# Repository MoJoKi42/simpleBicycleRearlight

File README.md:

# simpleBicycleRearlight

It's was a quick project to get finally a working rear light for my bicycle. It uses 10x VLMK31R1S2 LEDs (red LEDs from VISHAY) driven with ~13mA constant current. The TS2509 Buck-Converter regulates the output voltage to get the constant current (see circuit diagram!).
PCB and Circuit was made with KiCad.

It works with a standard 6V bicyle dynamo. At my setup it's starts with flashing at slow cycle rotation and goes over to a constant brightness at higher rotations. The minimum needed voltage is about 3.5-4V (RMS).

The final assembly on my bicycle

Test with some green LEDs

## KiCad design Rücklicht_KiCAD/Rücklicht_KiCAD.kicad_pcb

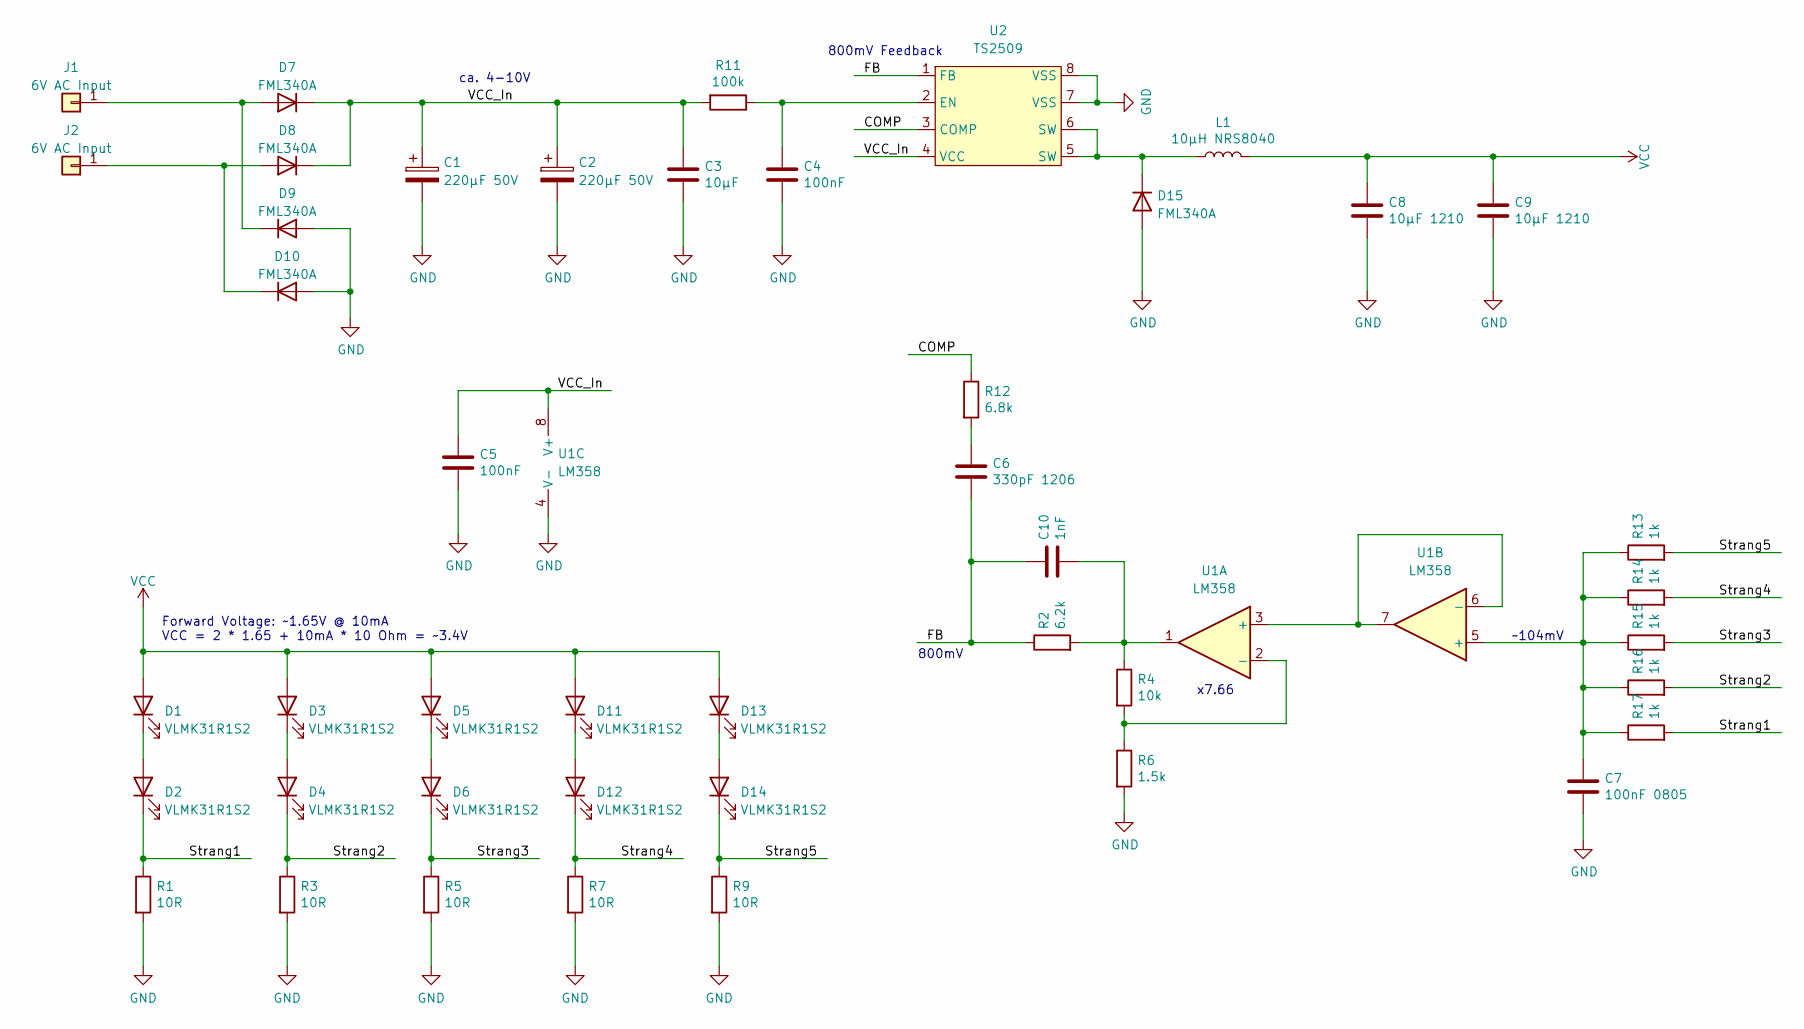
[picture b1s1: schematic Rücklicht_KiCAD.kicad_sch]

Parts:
C1, C2: 220µF 50V; C_Elec_10x10.2
C3: 10µF; C_1210_3225Metric_Pad1.33x2.70mm_HandSolder
C4, C5: 100nF; C_0805_2012Metric_Pad1.18x1.45mm_HandSolder
C6: 330pF 1206; C_1206_3216Metric_Pad1.33x1.80mm_HandSolder
C7: 100nF 0805; C_0805_2012Metric_Pad1.18x1.45mm_HandSolder
C8, C9: 10µF 1210; C_1210_3225Metric_Pad1.33x2.70mm_HandSolder
C10: 1nF; C_0805_2012Metric_Pad1.18x1.45mm_HandSolder
D1, D2, D3, D4, D5, D6, D11, D12, D13, D14: VLMK31R1S2; LED_PLCC-2
D7, D8, D9, D10, D15: FML340A; D_SMB_Handsoldering
J1, J2: 6V AC Input; TestPoint_Pad_3.0x3.0mm
L1: 10µH NRS8040; L_Taiyo-Yuden_NR-80xx_HandSoldering
R1, R3, R5, R7, R9: 10R; R_0805_2012Metric_Pad1.20x1.40mm_HandSolder
R2: 6.2k; R_0805_2012Metric_Pad1.20x1.40mm_HandSolder
R4: 10k; R_0805_2012Metric_Pad1.20x1.40mm_HandSolder
R6: 1.5k; R_0805_2012Metric_Pad1.20x1.40mm_HandSolder
R11: 100k; R_0805_2012Metric_Pad1.20x1.40mm_HandSolder
R12: 6.8k; R_0805_2012Metric_Pad1.20x1.40mm_HandSolder
R13, R14, R15, R16, R17: 1k; R_0805_2012Metric_Pad1.20x1.40mm_HandSolder
U1: LM358; SO-8_3.9x4.9mm_P1.27mm
U2: TS2509; SO-8_3.9x4.9mm_P1.27mm

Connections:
/COMP: R12.1, U2.3 (COMP)
/FB: C6.2, C10.1, R2.1, U2.1 (FB)
/Strang1: D2.1 (K), R1.1, R17.2
/Strang2: D4.1 (K), R3.1, R16.2
/Strang3: D6.1 (K), R5.1, R15.2
/Strang4: D12.1 (K), R7.1, R14.2
/Strang5: D14.1 (K), R9.1, R13.2
/VCC_In: C1.1, C2.1, C3.1, C5.1, D7.1 (K), D8.1 (K), R11.2, U1.8 (V+), U2.4 (VCC)
GND: C1.2, C2.2, C3.2, C4.2, C5.2, C7.2, C8.2, C9.2, D9.2 (A), D10.2 (A), D15.2 (A), R1.2, R3.2, R5.2, R6.2, R7.2, R9.2, U1.4 (V-), U2.7 (VSS), U2.8 (VSS)
unnamed: C4.1, R11.1, U2.2 (EN)
unnamed: C6.1, R12.2
unnamed: C7.1, R13.1, R14.1, R15.1, R16.1, R17.1, U1.5 (+)
unnamed: C10.2, R2.2, R4.1, U1.1
unnamed: D1.1 (K), D2.2 (A)
unnamed: D3.1 (K), D4.2 (A)
unnamed: D5.1 (K), D6.2 (A)
unnamed: D7.2 (A), D9.1 (K), J1.1
unnamed: D8.2 (A), D10.1 (K), J2.1
unnamed: D11.1 (K), D12.2 (A)
unnamed: D13.1 (K), D14.2 (A)
unnamed: D15.1 (K), L1.1, U2.5 (SW), U2.6 (SW)
unnamed: R4.2, R6.1, U1.2 (-)
unnamed: U1.3 (+), U1.6 (-), U1.7
VCC: C8.1, C9.1, D1.2 (A), D3.2 (A), D5.2 (A), D11.2 (A), D13.2 (A), L1.2

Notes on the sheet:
Forward Voltage: ~1.65V @ 10mA VCC = 2 * 1.65 + 10mA * 10 Ohm = ~3.4V
ca. 4-10V
800mV Feedback
800mV
x7.66
~104mV

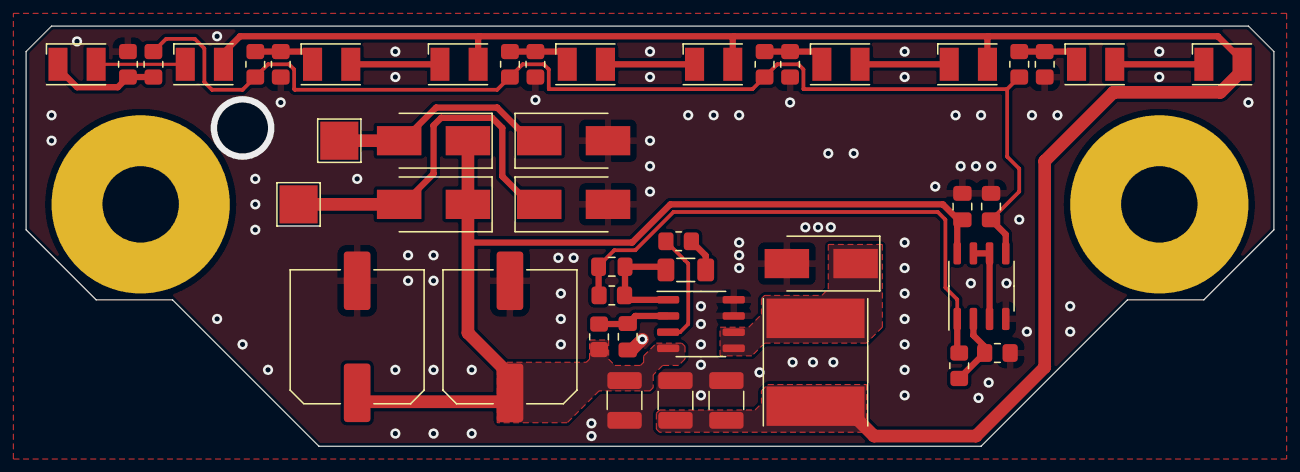
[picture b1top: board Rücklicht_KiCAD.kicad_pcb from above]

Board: 2 copper layers, 98.0 x 33.0 mm, 45 parts (0 on the bottom side), 24 nets.
